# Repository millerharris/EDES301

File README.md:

<h1>EDES301</h1>
Repository for EDES301 course work

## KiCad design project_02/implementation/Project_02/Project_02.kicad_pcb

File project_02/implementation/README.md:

<h1>
  Implementation Files
</h1>
<p>This directory holds the KiCad Library for all components needed in this project. This includes electical and mechanical components. They are all taken from the EDES301 canvas other than the driver, which was made myself based on this datasheet: https://www.pololu.com/product/1182
</p>

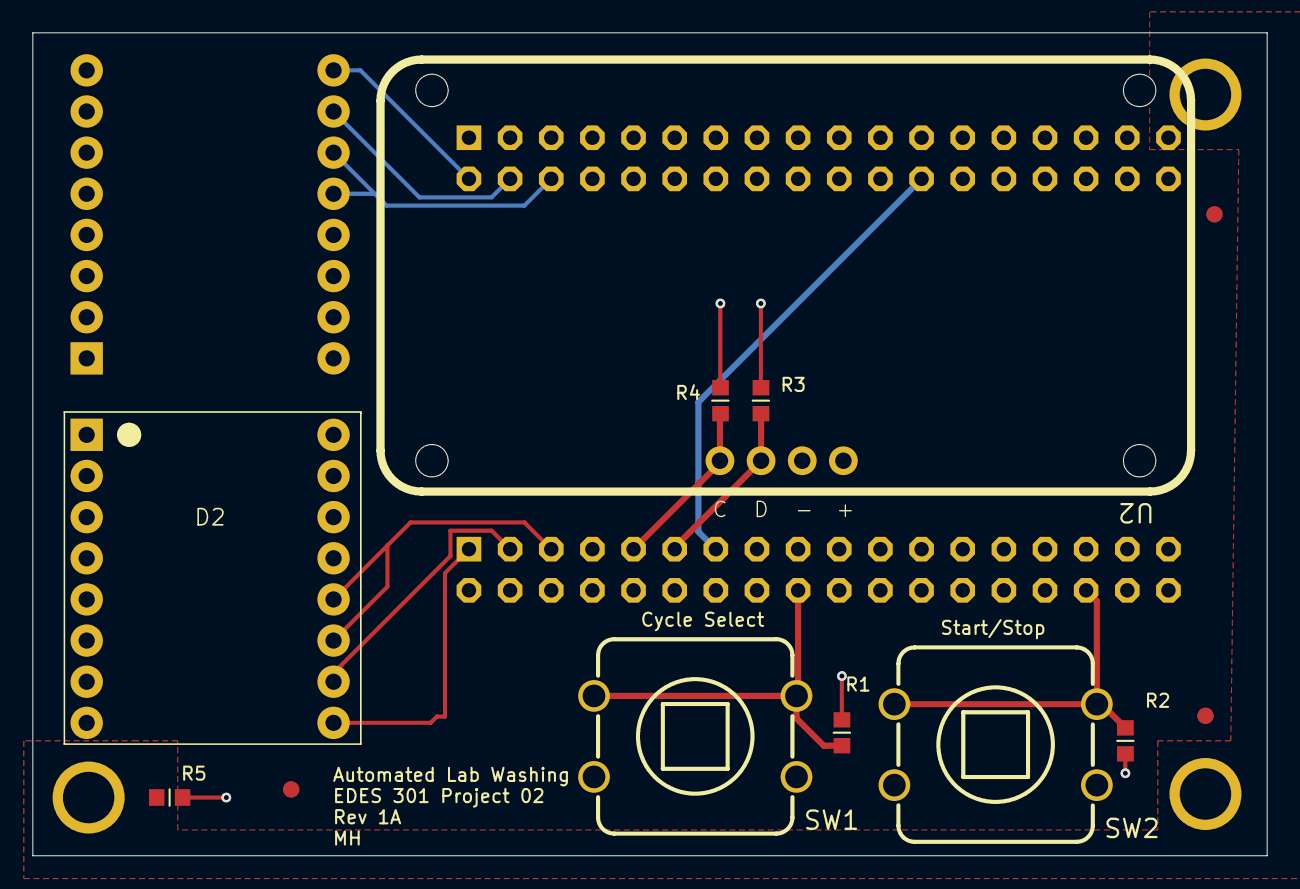
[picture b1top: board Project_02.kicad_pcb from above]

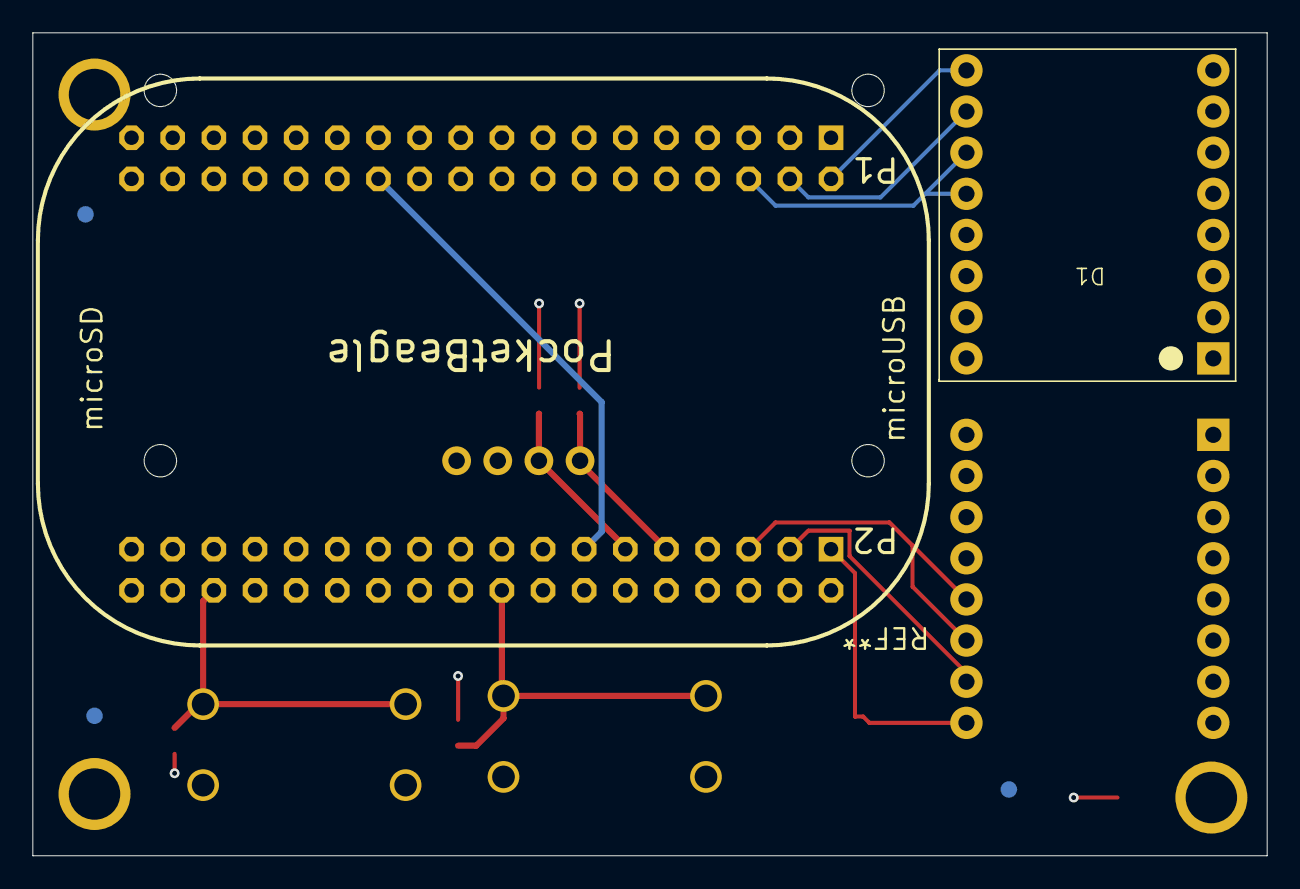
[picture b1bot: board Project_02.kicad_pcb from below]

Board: 4 copper layers, 76.2 x 50.8 mm, 20 parts (5 on the bottom side), 14 nets.

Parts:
D1, D2: DRIVER
FUD1, FUD2, FUD3, FUD4, FUD5, FUD6: FIDUCIAL_40MIL
M1, M3, M4: MOUNTING_HOLE
R1, R2, R3, R4, R5: R0603
SW1, SW2: BUTTON_12.5MM
U1: POCKETBEAGLE
U2: 0.56_HEX_BACKPACK

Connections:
+3V3: D1.7 (VDD), D2.7 (VDD), R1.2, R2.2, R3.2, R4.2, U1.P1_14 (3.3V@1), U1.P2_23 (3.3V@2), U2.VCC
+5V: D1.1 (VMOT), D2.1 (VMOT), U1.P1_24 (VOUT@1), U1.P2_13 (VOUT@2)
/GPIO_B1: R1.1, SW1.1, SW1.3, U1.P2_18 (GPIO47)
/GPIO_B2: R2.1, SW2.1, SW2.3, U1.P2_32 (PRU0.2)
/GPIO_M1_DIR: D1.16 (DIR), U1.P1_02 (AIN6(3.3V)GPIO87)
/GPIO_M1_SLEEP: D1.13 (RESET), D1.14 (SLEEP), U1.P1_06 (SPI0.CS)
/GPIO_M1_STEP: D1.15 (STEP), U1.P1_04 (GPIO89)
/GPIO_M2_DIR: D2.16 (DIR), U1.P2_01 (PWM1A)
/GPIO_M2_SLEEP: D2.13 (RESET), D2.14 (SLEEP), U1.P2_05 (UART4.RX)
/GPIO_M2_STEP: D2.15 (STEP), U1.P2_03 (GPIO23)
/I2C_SCL: R4.1, U1.P2_09 (I2C1.SCL), U2.SCL
/I2C_SDA: R3.1, U1.P2_11 (I2C1.SDA), U2.SDA
GND: D1.2 (GND), D1.8 (GND), D1.9 (ENABLE), D1.10 (MS1), D1.11 (MS2), D1.12 (MS3), D2.2 (GND), D2.8 (GND), D2.9 (ENABLE), D2.10 (MS1), D2.11 (MS2), D2.12 (MS3), R5.1, SW1.2, SW1.4, SW2.2, SW2.4, U1.P1_15 (GND@1), U1.P1_16 (GND@2), U1.P1_22 (GND@3), U1.P2_15 (GND@4), U1.P2_21 (GND@5), U2.GND
GNDPWR: M1.1 (1_1), M3.1 (1_1), M4.1 (1_1), R5.2

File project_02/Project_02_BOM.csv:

"Id";"Designator";"Footprint";"Quantity";"Designation";"Supplier and ref";
1;"D1, D2";"DRIVER";2;"~";;;
2;"FUD1, FUD2, FUD3, FUD4, FUD5, FUD6";"FIDUCIAL_40MIL";6;"~";;;
3;"M1, M3, M4";"MOUNTING_HOLE";3;"~";;;
4;"R1, R2, R3, R4, R5";"R0603";5;"~";;;
5;"SW1, SW2";"BUTTON_12.5MM";2;"~";;;
6;"U1";"POCKETBEAGLE";1;"~";;;
7;"U2";"0.56_HEX_BACKPACK";1;"~";;;

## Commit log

2026-02-05 Updating README.md
2026-02-23 Create docs
2026-02-24 commit simple_calc.py
2026-02-24 Adding simple calc updates
2026-02-24 needed to add my name
2026-02-24 Blinking Light Question 2
2026-02-24 comments
2026-02-24 ahhh
2026-02-24 sorry for last commit message
2026-02-24 button code for part 3
2026-02-24 forgot to add my name so added it
2026-03-02 Add files via upload
    Here is the updated power system
2026-04-19 Project Code
2026-04-23 working final code with motors and timer
